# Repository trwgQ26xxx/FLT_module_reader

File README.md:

# Fiat Lancia Tester \ Alfa Romeo Tester \ Check Up 1 module reader

Dedicated module reader for FLT\ART\CU-1 ROMs archiving.

Contact : trwgQ {leechers not welcome} 26 {remove spaces} xxx {remove spaces} {at} proton {dot} me

# Disclaimer

I do not consent to the use of all or part of the project for commercial purposes!

Nie wyrażam zgody na wykorzystanie całości bądź części projektu w celach zarobkowych!

# License

Shield: [![CC BY-NC-SA 4.0][cc-by-nc-sa-shield]][cc-by-nc-sa]

This work is licensed under a
[Creative Commons Attribution-NonCommercial-ShareAlike 4.0 International License][cc-by-nc-sa].

[![CC BY-NC-SA 4.0][cc-by-nc-sa-image]][cc-by-nc-sa]

[cc-by-nc-sa]: http://creativecommons.org/licenses/by-nc-sa/4.0/
[cc-by-nc-sa-image]: https://licensebuttons.net/l/by-nc-sa/4.0/88x31.png
[cc-by-nc-sa-shield]: https://img.shields.io/badge/License-CC%20BY--NC--SA%204.0-lightgrey.svg

# Directories organization

- **firmware** - MCU firmware, written in C.
- **pc_software** - PC software, written in Python.
- **PCB** - Reader PCB project, designed in KiCad.
- **ADAPTERS** - Adapter PCB projects, designed in KiCad.
- **DS** - data sheets of used components

# Usage

| Windows | Linux | macOS |
| --- | --- | --- |
| reader COM[number] | ./reader /dev/ttyUSB[number] | ./reader /dev/wchusbserial[number] |

For example:

| Windows | Linux | macOS |
| --- | --- | --- |
| reader COM1 | ./reader /dev/ttyUSB0 | ./reader /dev/wchusbserial300 |

where */dev/wchusbserial300* (on macOS), */dev/ttyUSB0* (on Linux) or *COM1* (on Windows) should be actual serial port name of connected ROM reader.

# Basic instructions

1. (optional step) *search_ports* script can be used to identify ROM reader serial port name.

The ROM reader uses the CH340 serial chip, which can be identified by the VID/PID values of 1A86/7523, respectively.

2. Connect the ROM reader to the PC. Running the program on a PC without a connected module will result in an error.

3. If a module is connected, the reader detects which ROMs are present in the connected module. In this example, we have a module with all three (**ROM A, B, and C**). If at least one ROM is installed (which will always be the case, since ROM B must be present), the program will prompt you to enter a prefix for the files that will be saved on the PC. I entered *M99A_IT* as an example. After confirming by pressing Enter, the ROM data dumping process begins:

4. Data integrity is continuously checked using CRC while downloading individual blocks (each block is 512 bytes). **In most cases, it may be advisable to repeat the dumping operation twice, disconnecting and reconnecting the ROM module to clean the contacts slightly.** Finally, individual files containing the ROM data are saved to the PC:

The process is similar for other modules. Here is an example if the module contains only **ROM A and B**:

or **ROM B** only:

The program reads the contents of only the ROMs that are present in the module.

# RAM adapter

The RAM adapter is used for SRAM testing. It was primarily constructed to test the M48Z02 (used in FLT/ART) and the M48T02 (used in CU-1). The RAM adapter takes the form of a standard FLT ROM module. Additionally, it requires a connection to a supplementary 2-pin connector with the #WR signal, which is not present on the DSUB-25 connector of the ROM.

Before usage, the RAM adapter must be configured to the correct RAM variant using solder bridges (SB1 - SB3) on the PCB. The configuration is as follows:

| RAM | Size | SB1 | SB2 | SB3 |
| --- | ---- | --- | --- | --- |
| M48T02, M48T12, M48Z02 and M48Z12 | 2kB | OFF | 1-2 | 1-2 |
| M48T08, M48T18, M48Z08 and M48Z18 | 8kB | OFF | 1-2 | 2-3 |
| 62256 | 32kB | ON | 2-3 | 2-3 |

The supported commands are:

* *RAM_test ram_type serial_port*, for example: ./RAM_test M48T02 /dev/ttyUSB0

This command tests the SRAM battery and SRAM memory. The supported SRAM types (*ram_type*) for this command are:

| *ram_type* | Size | Type |
| --- | --- | --- |
| M48T02 | 2kB | battery-backed SRAM with RTC |
| M48Z02 | 2kB | battery-backed SRAM |
| M48T08 | 8kB | battery-backed SRAM with RTC |
| M48Z08 | 8kB | battery-backed SRAM |
| S62256 | 32kB | SRAM |

* *RAM_clock_cmd ram_type command serial_port*, for example ./RAM_clock_cmd M48T02 set /dev/ttyUSB0

Executes an RTC-specific command. The command (*command*) can be:

| *command* | Description |
| --- | --- |
| start | Starts the internal oscillator and enables normal clock operation. |
| stop | Stops the internal oscillator, which saves battery power if the SRAM is left on the shelf for an extended period. |
| set | Sets the current time. |
| reset | Resets all registers, stops the internal oscillator, and sets the time to 0:0:0 on 1-1-2000. |

The supported SRAM types for this command are:

| *ram_type* | Size | Type |
| --- | --- | --- |
| M48T02 | 2kB | battery-backed SRAM with RTC |
| M48T08 | 8kB | battery-backed SRAM with RTC |

* *RAM_clock_read ram_type serial_port*, for example ./RAM_clock_read M48T02 /dev/ttyUSB0

Retrieves the time from the SRAM RTC and prints it on the screen in an infinite loop at a rate of twice per second. Use Ctrl-C to stop the execution of this command.

The supported SRAM types for this command are:

| *ram_type* | Size | Type |
| --- | --- | --- |
| M48T02 | 2kB | battery-backed SRAM with RTC |
| M48T08 | 8kB | battery-backed SRAM with RTC |

# Complete procedure to test battery-backed RAM

1. Use *RAM_test* to check the RAM battery and RAM memory cells.
2. If the RAM has an RTC:

- Execute the *reset command* to reset the RAM clock.

- Execute the *start command** to starts the internal oscillator and enable normal clock operation.

- Execute the *set command* to set the current time.

- Run *RAM_clock_read* to verify both the validity of the time and that it increments. If both conditions are met, the RTC is functioning properly.

# 87C510 adapter

The 87C510 adapter is designed for reading ROMs used in certain Bosch Motronic ECUs. The TMS87C510 is a 64 KB UV-erasable, multiplexed EPROM that supports both 8-bit and 16-bit output modes. The adapter is implemented in the form of a standard FLT ROM module, with the 87C510 configured and wired as ROMB.

# Notes

Atmega64A fusebits should be configured as follows:

| Extended | High | Low |
| --- | --- | --- |
| 0xFE | 0xC9 | 0x1F |

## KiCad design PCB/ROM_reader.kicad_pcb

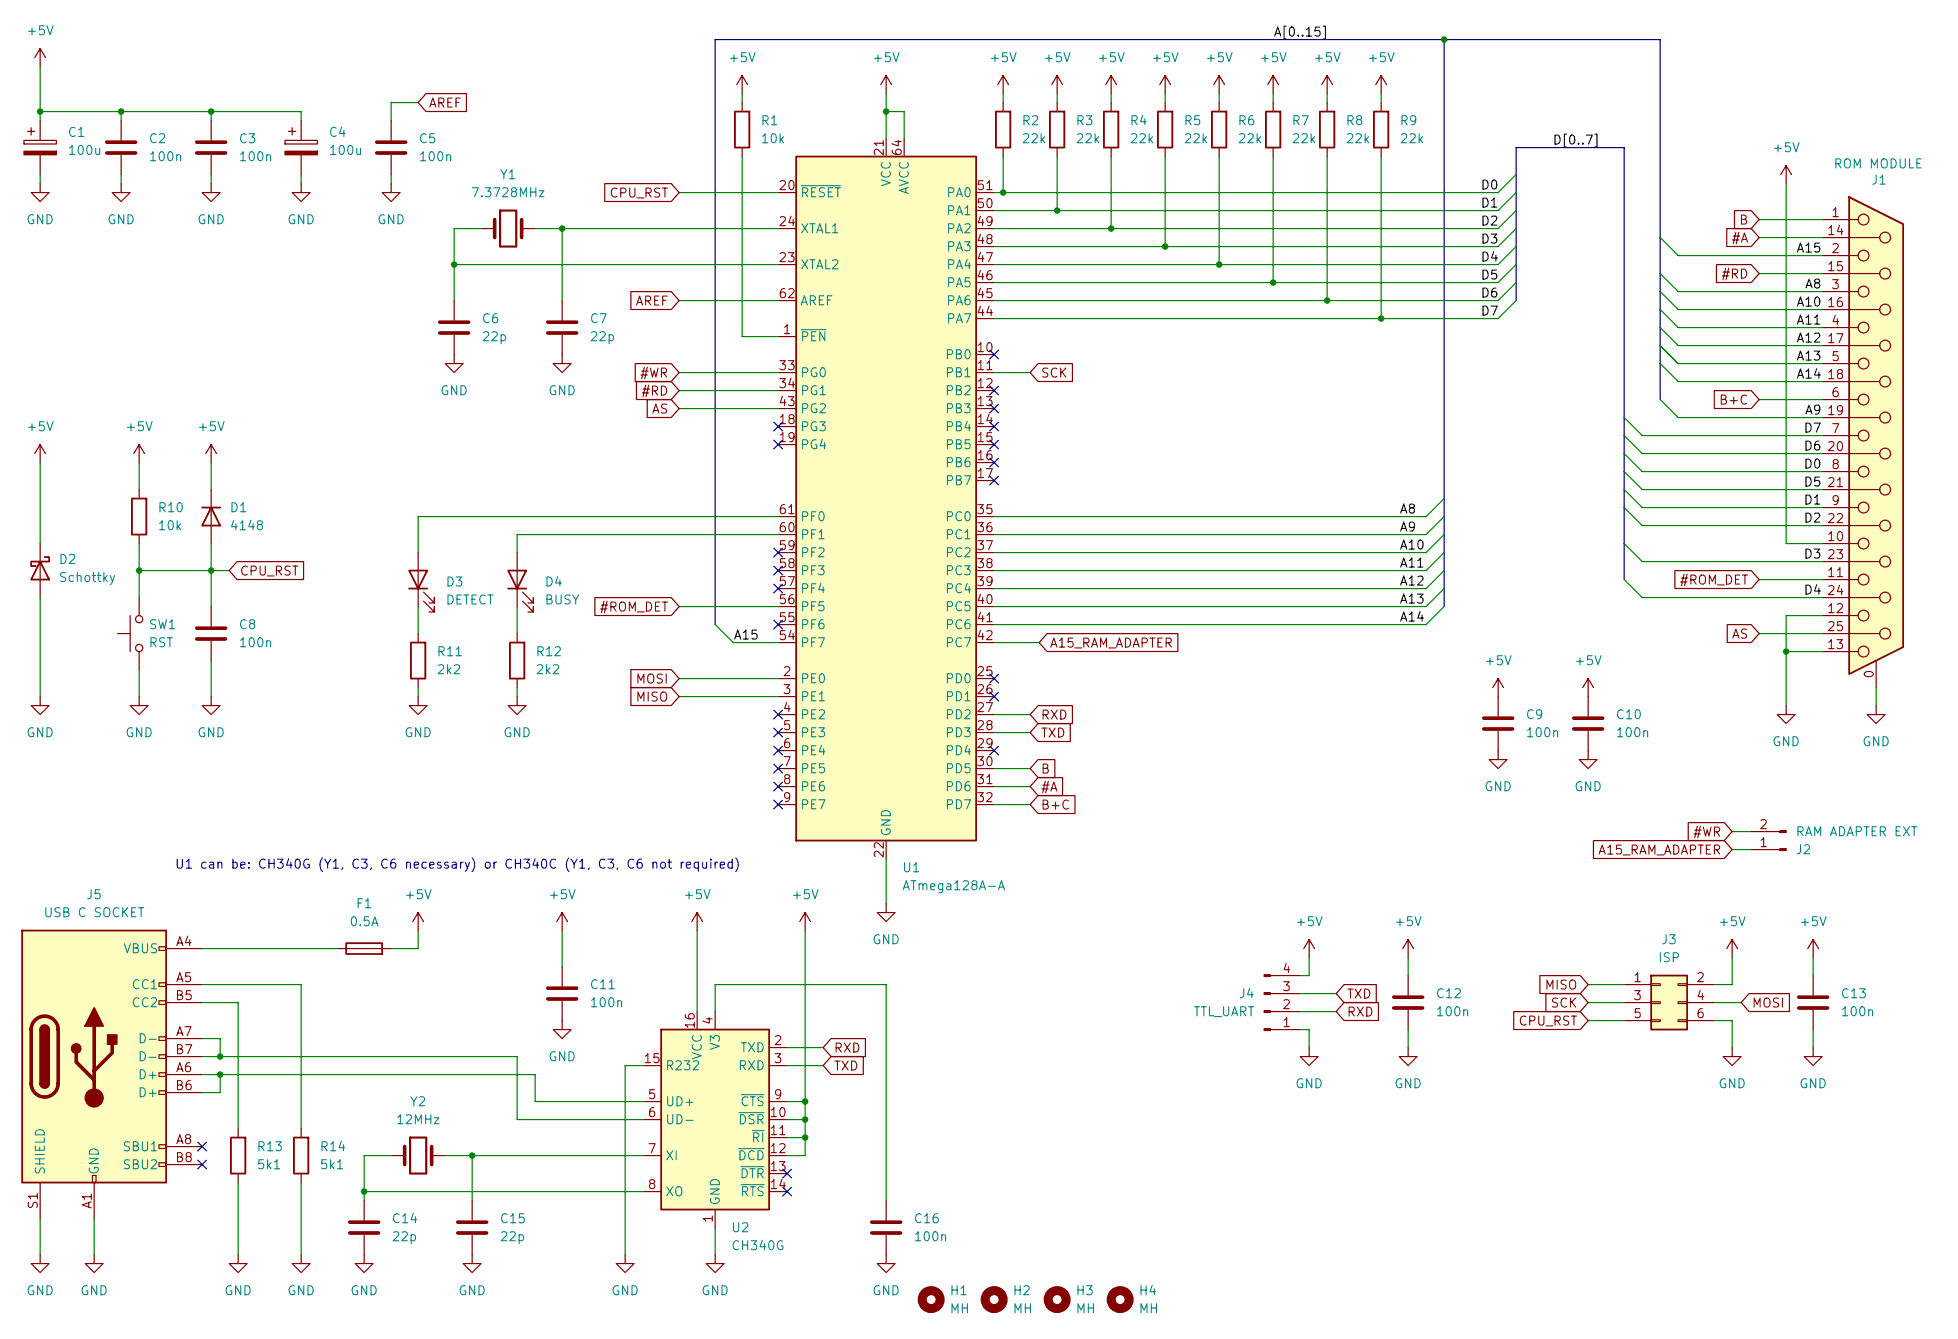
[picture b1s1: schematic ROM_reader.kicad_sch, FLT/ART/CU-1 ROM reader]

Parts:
C1, C4: 100u; CP_Elec_6.3x7.7
C2, C3, C5, C8, C9, C10, C11, C12, C13, C16: 100n; C_1206_3216Metric_Pad1.33x1.80mm_HandSolder
C6, C7, C14, C15: 22p; C_1206_3216Metric_Pad1.33x1.80mm_HandSolder
D1: 4148; D_SMA_Handsoldering
D2: Schottky; D_SMB_Handsoldering
D3: DETECT; LED_1206_3216Metric_Pad1.42x1.75mm_HandSolder
D4: BUSY; LED_1206_3216Metric_Pad1.42x1.75mm_HandSolder
F1: 0.5A; Fuse_2512_6332Metric_Pad1.52x3.35mm_HandSolder
H1, H2, H3, H4: MH; MountingHole_3.2mm_M3_DIN965
J1: ROM MODULE; DSUB-25_Socket_Horizontal_P2.77x2.84mm_EdgePinOffset4.94mm_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
J2: RAM ADAPTER EXT; PinHeader_1x02_P2.54mm_Horizontal
J3: ISP; PinHeader_2x03_P2.54mm_Horizontal
J4: TTL_UART; PinHeader_1x04_P2.54mm_Horizontal
J5: USB C SOCKET; USB_C_Receptacle_GCT_USB4105-xx-A_16P_TopMnt_Horizontal
R1, R10: 10k; R_1206_3216Metric_Pad1.30x1.75mm_HandSolder
R2, R3, R4, R5, R6, R7, R8, R9: 22k; R_1206_3216Metric_Pad1.30x1.75mm_HandSolder
R11, R12: 2k2; R_1206_3216Metric_Pad1.30x1.75mm_HandSolder
R13, R14: 5k1; R_1206_3216Metric_Pad1.30x1.75mm_HandSolder
SW1: RST; SW_PUSH_6mm
U1: ATmega128A-A; TQFP-64_14x14mm_P0.8mm
U2: CH340G; SOIC-16_3.9x9.9mm_P1.27mm
Y1: 7.3728MHz; Crystal_HC49-4H_Vertical
Y2: 12MHz; Crystal_HC49-4H_Vertical

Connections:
#A: J1.14, U1.31 (PD6)
#RD: J1.15, U1.34 (PG1)
#ROM_DET: J1.11, U1.56 (PF5)
#WR: J2.2, U1.33 (PG0)
+5V: C1.1, C2.1, C3.1, C4.1, C9.1, C10.1, C11.1, C12.1, C13.1, D1.1 (K), D2.1 (K), F1.2, J1.10, J3.2, J4.4, R1.2, R2.2, R3.2, R4.2, R5.2, R6.2, R7.2, R8.2, R9.2, R10.2, U1.21 (VCC), U1.52 (VCC), U1.64 (AVCC), U2.9 (~CTS), U2.10 (~DSR), U2.11 (~RI), U2.12 (~DCD), U2.16 (VCC)
/A8: J1.3, U1.35 (PC0)
/A9: J1.19, U1.36 (PC1)
/A10: J1.16, U1.37 (PC2)
/A11: J1.4, U1.38 (PC3)
/A12: J1.17, U1.39 (PC4)
/A13: J1.5, U1.40 (PC5)
/A14: J1.18, U1.41 (PC6)
/A15: J1.2, U1.54 (PF7)
/D0: J1.8, R2.1, U1.51 (PA0)
/D1: J1.9, R3.1, U1.50 (PA1)
/D2: J1.22, R4.1, U1.49 (PA2)
/D3: J1.23, R5.1, U1.48 (PA3)
/D4: J1.24, R6.1, U1.47 (PA4)
/D5: J1.21, R7.1, U1.46 (PA5)
/D6: J1.20, R8.1, U1.45 (PA6)
/D7: J1.7, R9.1, U1.44 (PA7)
A15_RAM_ADAPTER: J2.1, U1.42 (PC7)
AREF: C5.1, U1.62 (AREF)
AS: J1.25, U1.43 (PG2)
B: J1.1, U1.30 (PD5)
B+C: J1.6, U1.32 (PD7)
CPU_RST: C8.1, D1.2 (A), J3.5, R10.1, SW1.2, U1.20 (~RESET)
GND: C1.2, C2.2, C3.2, C4.2, C5.2, C6.2, C7.2, C8.2, C9.2, C10.2, C11.2, C12.2, C13.2, C14.2, C15.2, C16.2, D2.2 (A), J1.0 (PAD), J1.12, J1.13, J3.6, J4.1, J5.A1 (GND), J5.A12 (GND), J5.B1 (GND), J5.B12 (GND), J5.S1 (SHIELD), R11.1, R12.1, R13.1, R14.1, SW1.1, U1.22 (GND), U1.53 (GND), U1.63 (GND), U2.1 (GND), U2.15 (R232)
MISO: J3.1, U1.3 (PE1)
MOSI: J3.4, U1.2 (PE0)
unnamed: D3.2 (A), U1.61 (PF0)
unnamed: D3.1 (K), R11.2
unnamed: D4.2 (A), U1.60 (PF1)
unnamed: D4.1 (K), R12.2
unnamed: F1.1, J5.A4 (VBUS), J5.A9 (VBUS), J5.B4 (VBUS), J5.B9 (VBUS)
unnamed: J5.A5 (CC1), R14.2
unnamed: J5.B5 (CC2), R13.2
unnamed: C7.1, U1.24 (XTAL1), Y1.2
unnamed: C6.1, U1.23 (XTAL2), Y1.1
unnamed: R1.1, U1.1 (~PEN)
unnamed: J5.A6 (D+), J5.B6 (D+), U2.5 (UD+)
unnamed: J5.A7 (D-), J5.B7 (D-), U2.6 (UD-)
unnamed: C16.1, U2.4 (V3)
unnamed: C15.1, U2.7 (XI), Y2.2
unnamed: C14.1, U2.8 (XO), Y2.1
RXD: J4.2, U1.27 (PD2), U2.2 (TXD)
SCK: J3.3, U1.11 (PB1)
TXD: J4.3, U1.28 (PD3), U2.3 (RXD)

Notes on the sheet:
U1 can be: CH340G (Y1, C3, C6 necessary) or CH340C (Y1, C3, C6 not required)

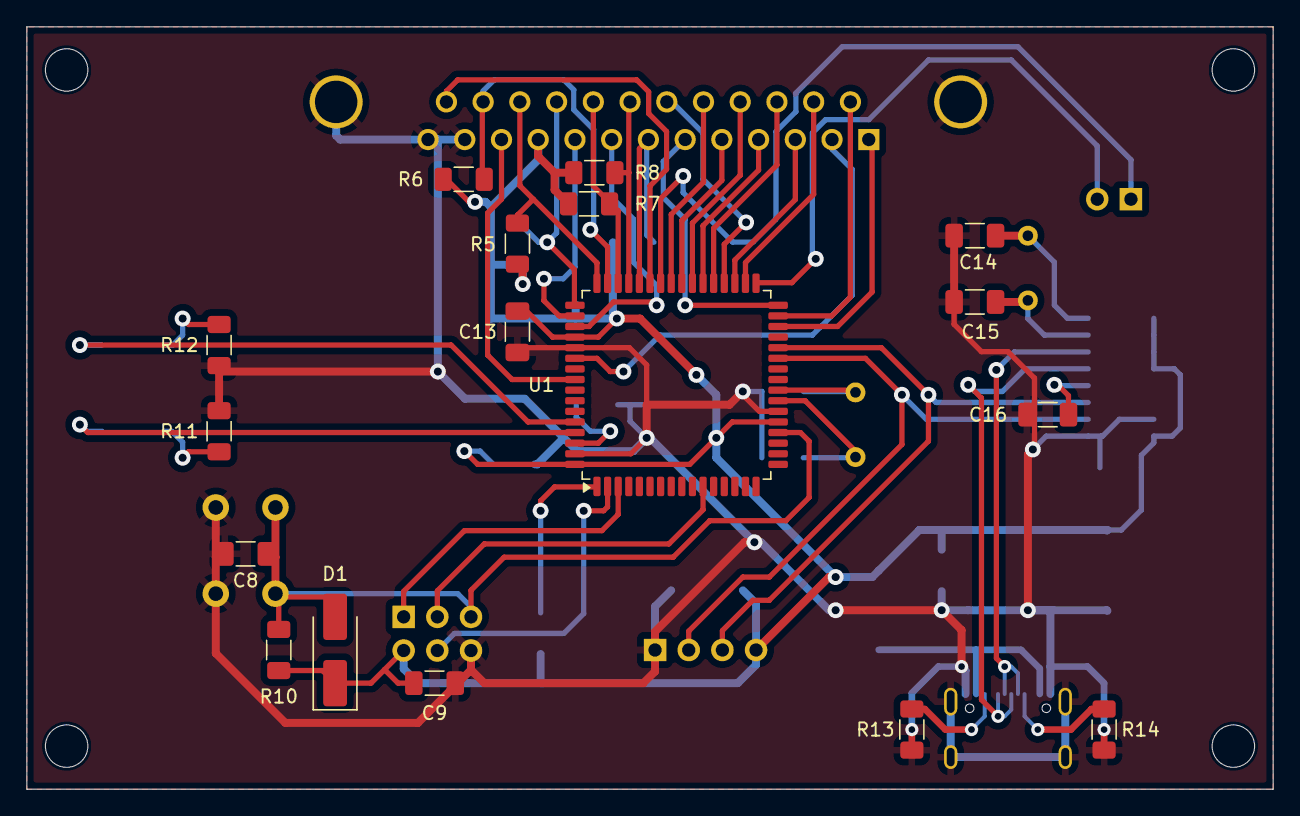
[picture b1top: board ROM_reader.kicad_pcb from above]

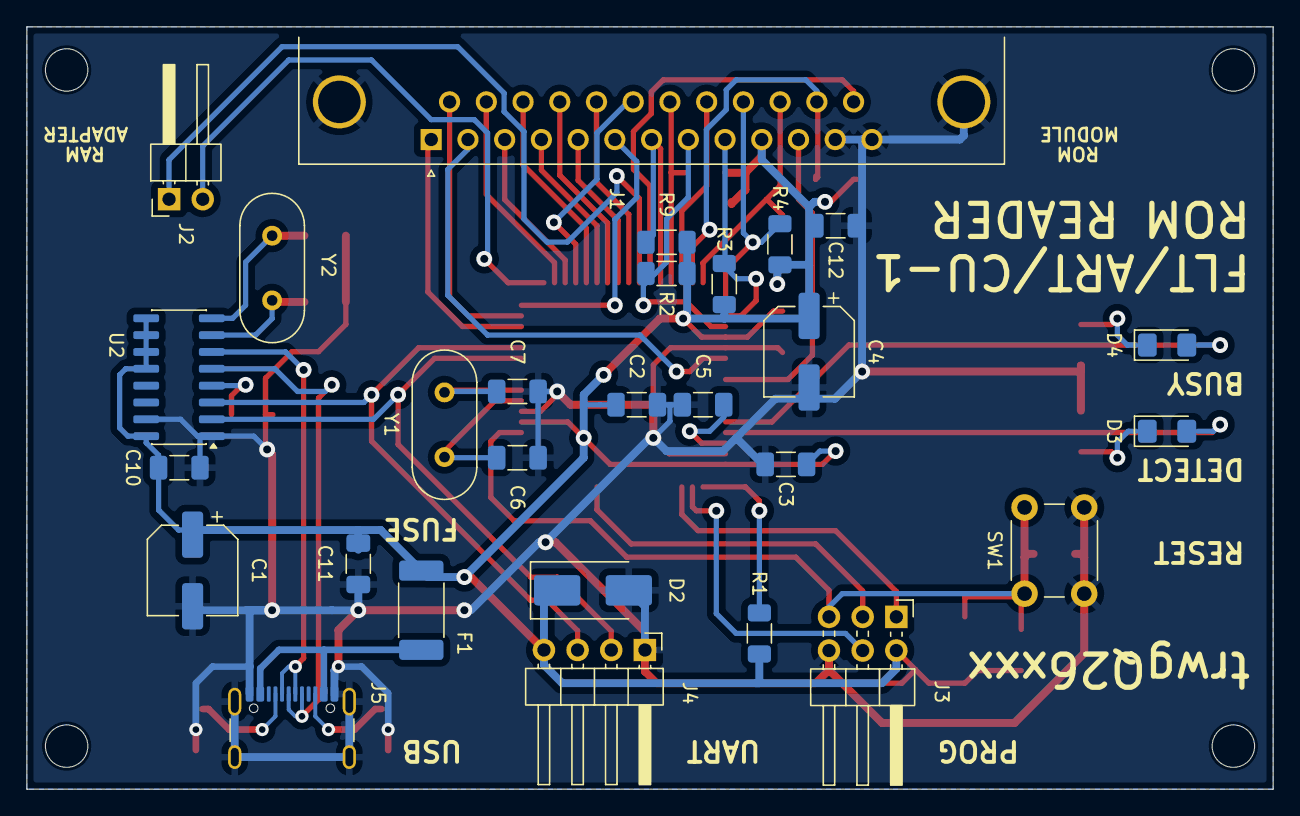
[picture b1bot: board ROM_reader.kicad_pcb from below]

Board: 2 copper layers, 94.0 x 57.5 mm, 49 parts (28 on the bottom side), 48 nets.

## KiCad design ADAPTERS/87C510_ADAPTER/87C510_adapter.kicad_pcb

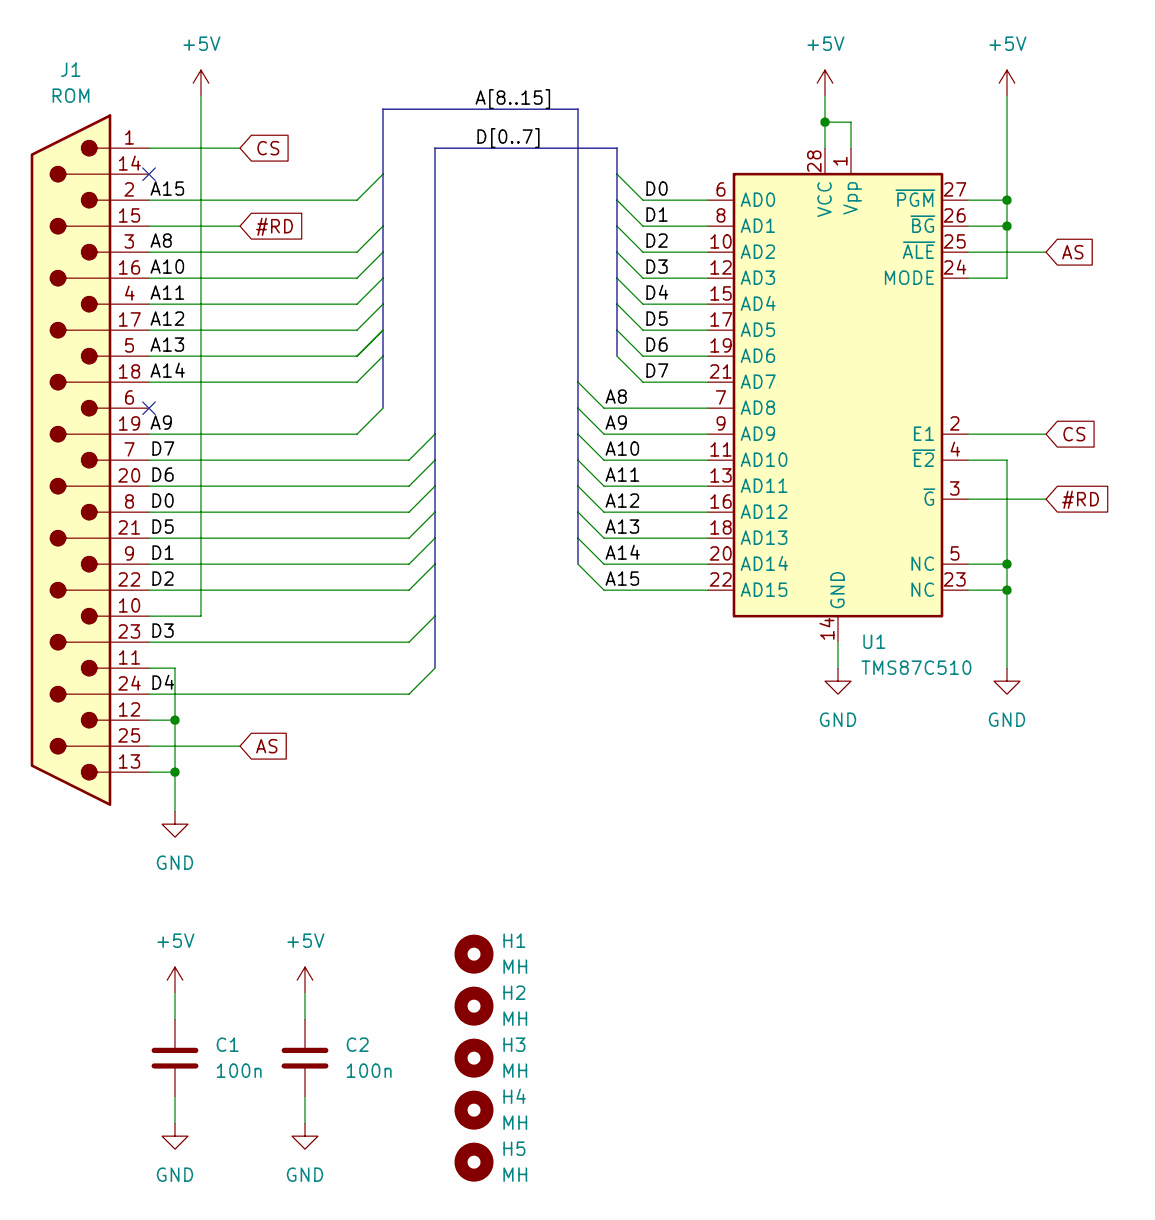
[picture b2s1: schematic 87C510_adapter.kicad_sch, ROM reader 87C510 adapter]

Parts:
C1, C2: 100n; C_1206_3216Metric_Pad1.33x1.80mm_HandSolder
H1, H2, H3, H4, H5: MH; MountingHole_3.2mm_M3_DIN965
J1: ROM; DSUB-25_Male_Horizontal_P2.77x2.84mm_EdgePinOffset4.94mm_Ho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
U1: TMS87C510; DIP_Socket-28_W11.9mm_W12.7mm_W15.24mm_W17.78mm_W18.5mm_3M_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

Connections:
#RD: J1.15, U1.3 (~G)
+5V: C1.1, C2.1, J1.10, U1.1 (Vpp), U1.24 (MODE), U1.26 (~BG), U1.27 (~PGM), U1.28 (VCC)
/A8: J1.3, U1.7 (AD8)
/A9: J1.19, U1.9 (AD9)
/A10: J1.16, U1.11 (AD10)
/A11: J1.4, U1.13 (AD11)
/A12: J1.17, U1.16 (AD12)
/A13: J1.5, U1.18 (AD13)
/A14: J1.18, U1.20 (AD14)
/A15: J1.2, U1.22 (AD15)
/D0: J1.8, U1.6 (AD0)
/D1: J1.9, U1.8 (AD1)
/D2: J1.22, U1.10 (AD2)
/D3: J1.23, U1.12 (AD3)
/D4: J1.24, U1.15 (AD4)
/D5: J1.21, U1.17 (AD5)
/D6: J1.20, U1.19 (AD6)
/D7: J1.7, U1.21 (AD7)
AS: J1.25, U1.25 (~ALE)
CS: J1.1, U1.2 (E1)
GND: C1.2, C2.2, J1.0, J1.11, J1.12, J1.13, U1.4 (~E2), U1.5 (NC), U1.14 (GND), U1.23 (NC)

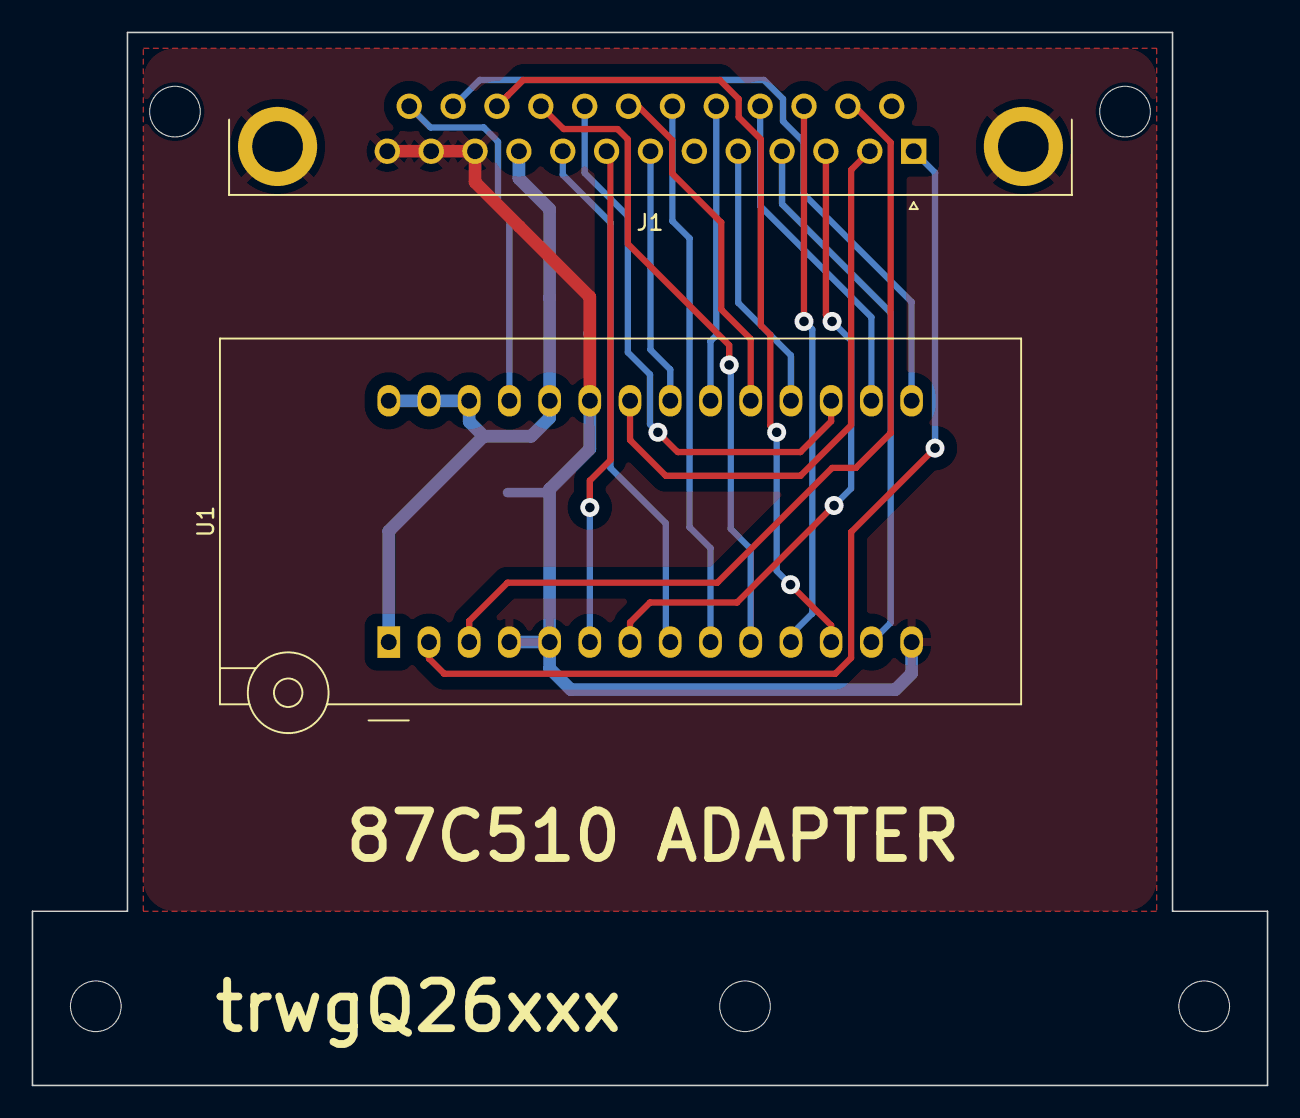
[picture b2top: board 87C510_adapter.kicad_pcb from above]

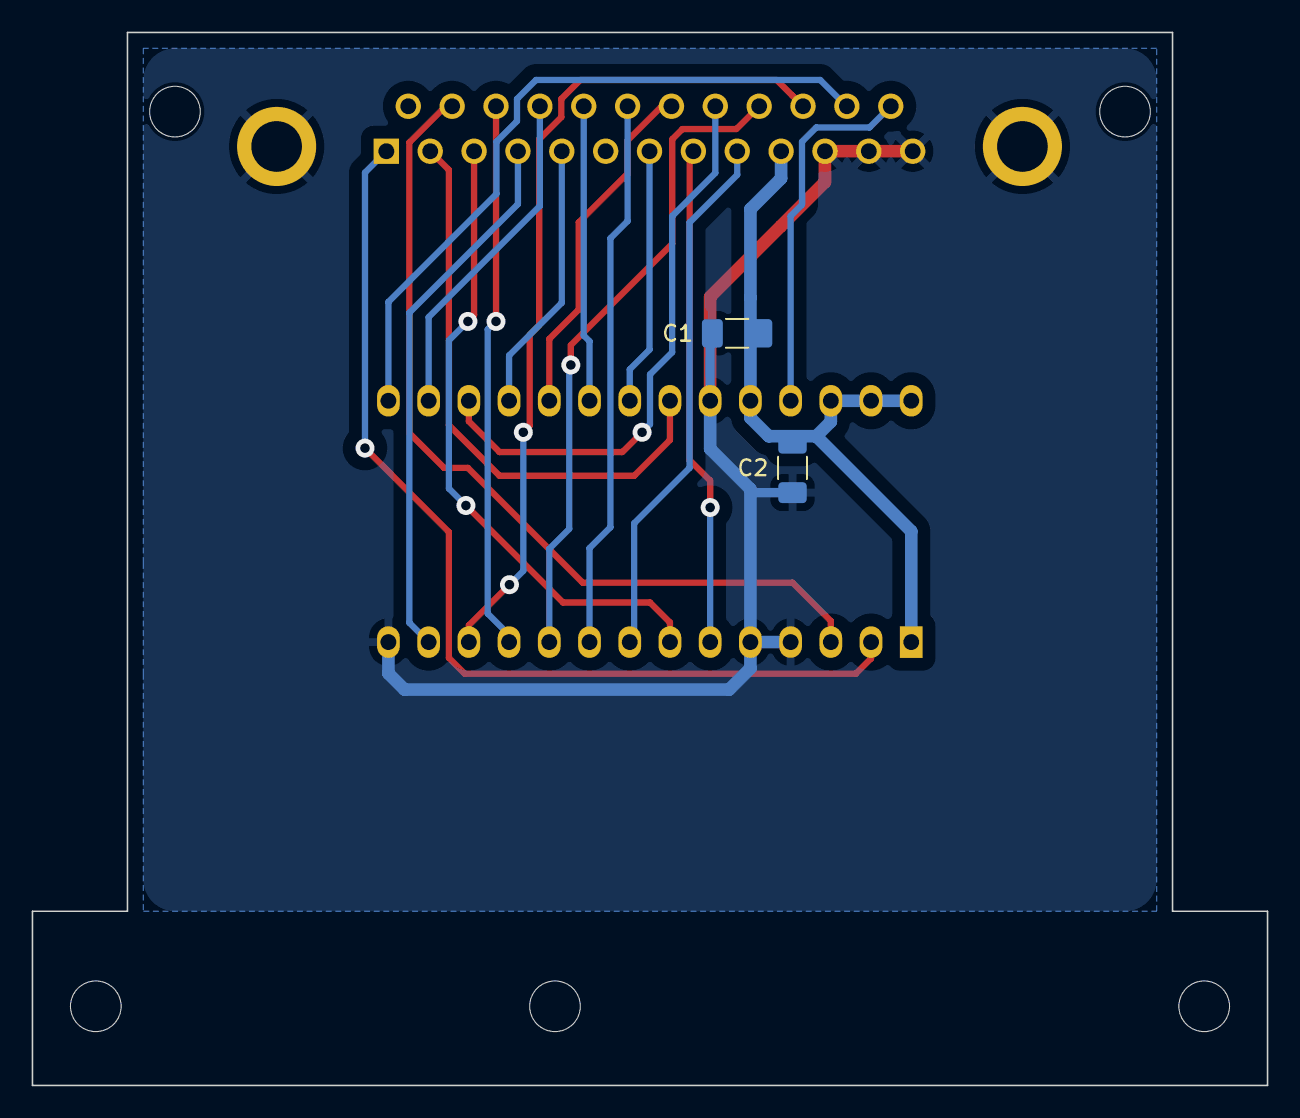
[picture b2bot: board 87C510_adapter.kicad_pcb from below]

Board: 2 copper layers, 78.0 x 66.5 mm, 9 parts (2 on the bottom side), 21 nets.

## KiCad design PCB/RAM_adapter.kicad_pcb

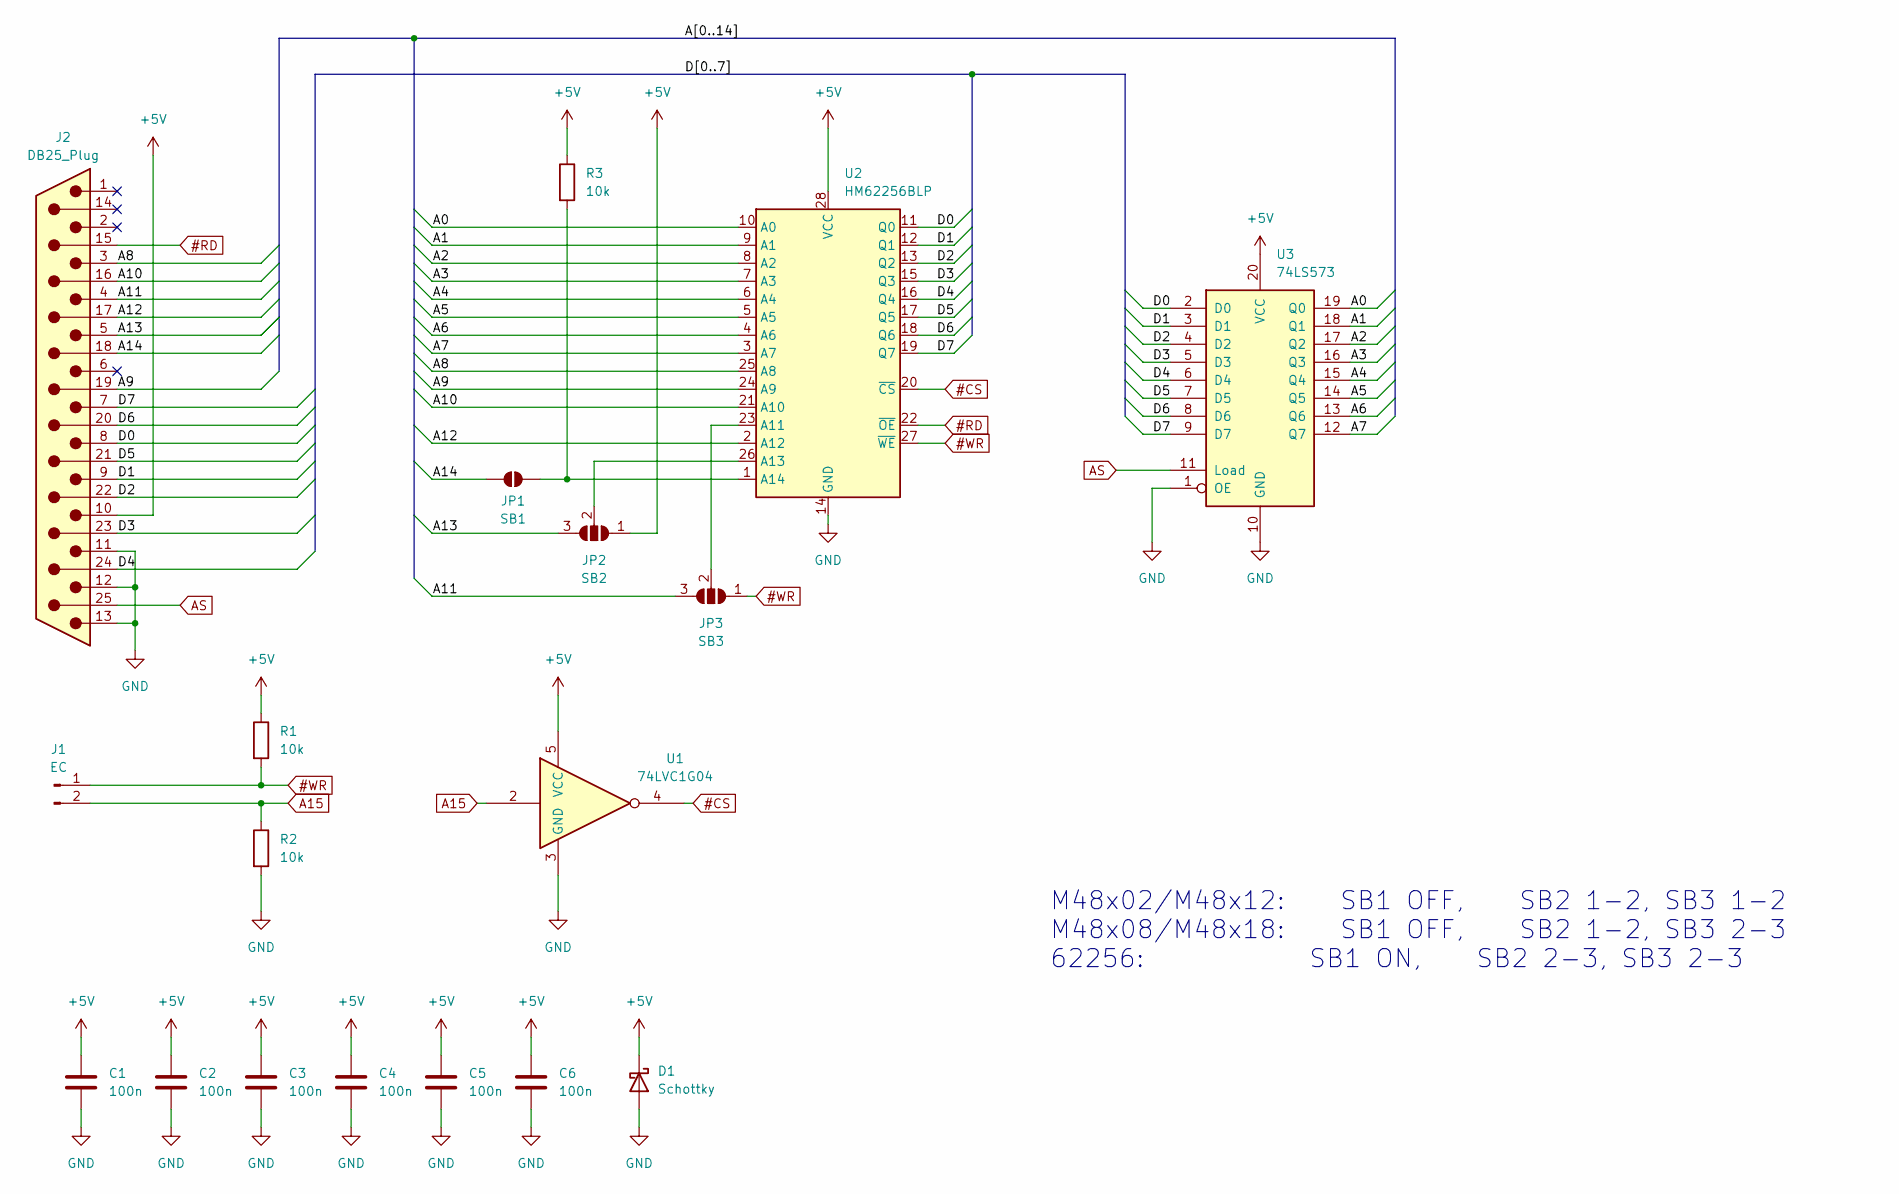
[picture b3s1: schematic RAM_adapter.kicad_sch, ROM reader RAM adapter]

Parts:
C1, C2, C3, C4, C5, C6: 100n; C_1206_3216Metric_Pad1.33x1.80mm_HandSolder
D1: Schottky; D_SMB_Handsoldering
J1: EC; PinHeader_1x02_P2.54mm_Vertical
J2: DB25_Plug; DSUB-25_Male_Horizontal_P2.77x2.84mm_EdgePinOffset4.94mm_Ho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
JP1: SB1; SolderJumper-2_P1.3mm_Open_RoundedPad1.0x1.5mm
JP2: SB2; SolderJumper-3_P1.3mm_Open_RoundedPad1.0x1.5mm
JP3: SB3; SolderJumper-3_P1.3mm_Open_RoundedPad1.0x1.5mm
R1, R2, R3: 10k; R_1206_3216Metric_Pad1.30x1.75mm_HandSolder
U1: 74LVC1G04; SOT-23-5_HandSoldering
U2: HM62256BLP; DIP_Socket-28_W11.9_W12.7_W15.24_W17.78_W18.5_3M_228-1277-0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
U3: 74LS573; SOIC-20W_7.5x12.8mm_P1.27mm

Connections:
#CS: U1.4, U2.20 (~CS)
#RD: J2.15, U2.22 (~OE)
#WR: J1.1, JP3.1 (A), R1.2, U2.27 (~WE)
+5V: C1.1, C2.1, C3.1, C4.1, C5.1, C6.1, D1.1 (K), J2.10, JP2.1 (A), R1.1, R3.1, U1.5 (VCC), U2.28 (VCC), U3.20 (VCC)
/A0: U2.10 (A0), U3.19 (Q0)
/A1: U2.9 (A1), U3.18 (Q1)
/A2: U2.8 (A2), U3.17 (Q2)
/A3: U2.7 (A3), U3.16 (Q3)
/A4: U2.6 (A4), U3.15 (Q4)
/A5: U2.5 (A5), U3.14 (Q5)
/A6: U2.4 (A6), U3.13 (Q6)
/A7: U2.3 (A7), U3.12 (Q7)
/A8: J2.3, U2.25 (A8)
/A9: J2.19, U2.24 (A9)
/A10: J2.16, U2.21 (A10)
/A11: J2.4, JP3.3 (B)
/A12: J2.17, U2.2 (A12)
/A13: J2.5, JP2.3 (B)
/A14: J2.18, JP1.2 (B)
/D0: J2.8, U2.11 (Q0), U3.2 (D0)
/D1: J2.9, U2.12 (Q1), U3.3 (D1)
/D2: J2.22, U2.13 (Q2), U3.4 (D2)
/D3: J2.23, U2.15 (Q3), U3.5 (D3)
/D4: J2.24, U2.16 (Q4), U3.6 (D4)
/D5: J2.21, U2.17 (Q5), U3.7 (D5)
/D6: J2.20, U2.18 (Q6), U3.8 (D6)
/D7: J2.7, U2.19 (Q7), U3.9 (D7)
A15: J1.2, R2.1, U1.2
AS: J2.25, U3.11 (Load)
GND: C1.2, C2.2, C3.2, C4.2, C5.2, C6.2, D1.2 (A), J2.11, J2.12, J2.13, R2.2, U1.3 (GND), U2.14 (GND), U3.1 (OE), U3.10 (GND)
unnamed: JP1.1 (A), R3.2, U2.1 (A14)
unnamed: JP2.2 (C), U2.26 (A13)
unnamed: JP3.2 (C), U2.23 (A11)

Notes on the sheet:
M48x02/M48x12: SB1 OFF, SB2 1-2, SB3 1-2 M48x08/M48x18: SB1 OFF, SB2 1-2, SB3 2-3 62256: SB1 ON, SB2 2-3, SB3 2-3

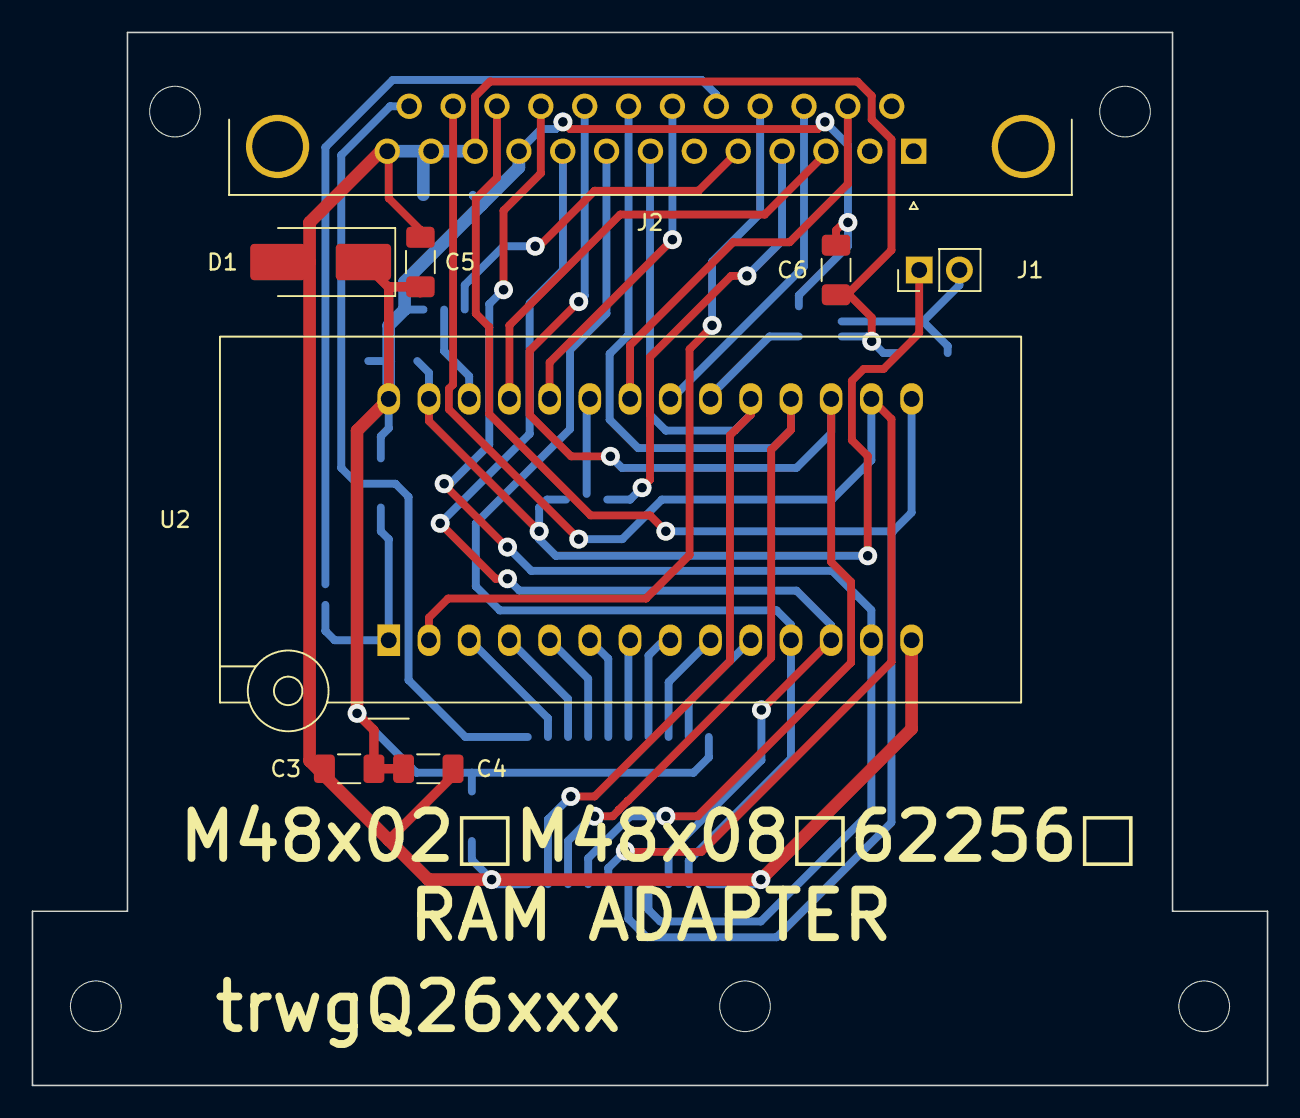
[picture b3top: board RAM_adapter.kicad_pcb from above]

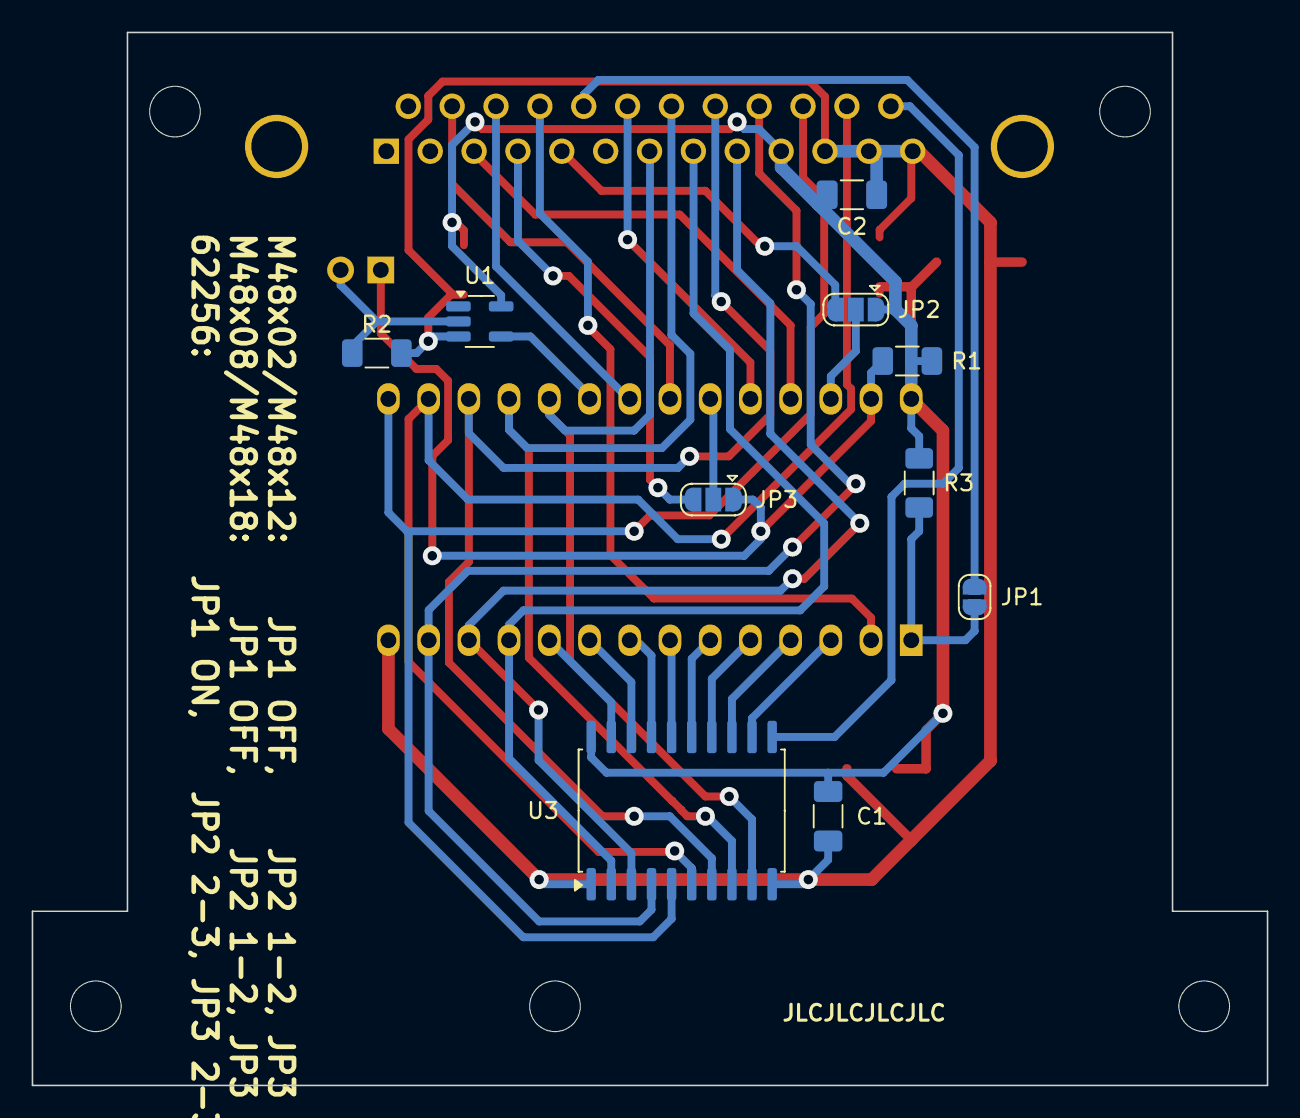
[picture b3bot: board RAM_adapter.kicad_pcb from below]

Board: 2 copper layers, 78.0 x 66.5 mm, 18 parts (10 on the bottom side), 33 nets.

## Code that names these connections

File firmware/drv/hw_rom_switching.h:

/* 
Project name:	FLT/ART/CU1 ROM Reader
Author: 		trwgQ26xxx
Date:			26.06.2024
Target MCUs:	ATmega64/ATmega64L/ATmega64A/ATmega128/ATmega128L/ATmega128A
Compiler:		AVR-GCC version 7.3.0
*/

/*
--- CONNECTIONS ---

BANK SWITCHING:
PD5 -> B
PD6 -> #A
PD7 -> B + C

ROM MODULE DETECTION:
PF5 -> #ROM_DET

A15 LINE MANAGEMENT:
PF7 -> A15

--- CONNECTIONS ---
*/

#ifndef _DRV_HW_ROM_SWITCHING_H
#define _DRV_HW_ROM_SWITCHING_H

#include <stdint.h>

/* ROM selection */
#define DISABLE_ALL_ROMS		do{ PORTD &= ~((1 << 7) | (1 << 5)); PORTD |= (1 << 6);	}while(0)
#define ENABLE_A_ROM			do{ PORTD &= ~((1 << 7) | (1 << 6) | (1 << 5));			}while(0)
#define ENABLE_B_ROM			do{ PORTD |= (1 << 7) | (1 << 6) | (1 << 5);			}while(0)
#define ENABLE_C_ROM			do{ PORTD &= ~(1 << 5); PORTD |= (1 << 7) | (1 << 6);	}while(0)

/* ROM module detection */
#define IS_ROM_MODULE_PRESENT	(!(PINF & (1 << 5)))

/* A15 pin switching */
#define CONFIGURE_A15_AS_OUT	do{ DDRF |= (1 << 7);									}while(0)
#define SET_A15_TO_HIGH			do{ PORTF |= (1 << 7);									}while(0)
#define SET_A15_TO_LOW			do{ PORTF &= ~(1 << 7);									}while(0)

/* Initialize function */
void Init_ROMs(void);

void Init_unused_pins(void);

#endif

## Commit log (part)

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2024-04-20 PCB project added
2024-04-20 README.md updated
2024-04-21 Hardware definitions added
2024-06-22 Adding prepared MCU firmware
2024-06-22 Adding PC software & compiled version for Linux x64
2024-06-22 Replaced preview with actual photos
2024-06-22 Updated README.md, added basic instructions
2024-06-22 Cosmetic changes
2024-06-26 Renamed compile options for 7.3728MHz and 9.216MHz crystals
2024-06-26 Added project info to all firmware files
2024-06-26 Verify script added
2024-06-27 Added compiled PC software for Windows
2024-06-27 Added datasheet of used ICs
2024-08-24 License information added
2024-08-24 RAM adapter PCB project for RAM testing added
2025-01-21 Revised RAM adapter PCB
2025-01-21 Firmware updated, added RAM test procedures
2025-01-21 Datasheets for M48x02 battery-backed SRAMs added
2025-01-21 RAM test PC scripts added
2025-01-21 Minor refactor
2025-01-21 Random data test added as second pass of RAM test procedure
2025-01-21 MacOS packed version added
2025-01-21 Added version strings for each script
2025-01-21 Updated .gitignore
2025-01-21 ROM reader project PCBs updated
2025-01-21 ADC disabled. Procedures removed as were not functional. Unused pins configured as inputs with pull-ups
2025-01-22 Datasheets update
2025-01-22 Minor changes in text placement on PCB, comments. Revision updated to B
2025-01-31 Added instructions related to the RAM adapter
2025-01-31 Minor update
2025-01-31 Added M48T08 datasheet
2025-02-05 Dependency on the libscrc library removed
2025-02-05 Update of the packed version for Linux
2025-02-05 PCB project update: pull-up resistors added for D0-D7 data lines
2025-02-09 Gitignore updated
2025-02-10 Minor updates
2025-03-01 9.216MHz option dropped, only 7.3728MHz crystal would be supported from now on
2025-03-01 UART baudrate increased from 57600 to 115200
2025-03-12 Minor improvements
2025-03-12 Added WDT configured for 0.52s
2025-03-12 Added script to configure fuse bits, WDTON fuse added
2025-03-12 Changed timeout for RAM-test, as 0.5s was not sufficient for 32k test
2025-03-12 AVR-GCC version updated
2025-03-18 Reintroduced the system call, as its absence caused missing colors on the Windows console
2025-03-18 Windows software updated
2025-10-15 Photos updated
2026-01-24 Added 87C510 adapter, RAM adapter moved to new ADAPTERS directory
2026-01-24 Fixed 87C510 project, as inverter gate for ALE signal was not required
2026-01-24 Added more photos of 87C510 adapter
2026-01-24 Added new datasheets
2026-04-11 Datasheets updated
